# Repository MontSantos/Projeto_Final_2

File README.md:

# Do Material ao Digital

## Implementação de Jogos e Utilitários em Hardware Reprogramável

**Por: Guilherme Santos**  
Repositório de Projeto Final de Graduação em Engenharia de Computação.

Nota Final: 10,0 / 10,0

---

Este repositório disponibiliza todos os materiais utilizados e desenvolvidos ao longo do projeto, incluindo:

- Esquemáticos e layouts das PCBs desenvolvidas para suporte de periféricos
- Data sheets dos principais componentes utilizados
- Implementações de protocolos de comunicação de vídeo (VGA) e teclado (PS/2)
- Códigos de teste para validação de módulos
- Códigos completos dos projetos implementados no FPGA
- Simulações dos circuitos desenvolvidos

---

## Estrutura do Repositório

Este repositório está organizado da seguinte forma:

- **Datasheets**  
  Data sheets dos componentes utilizados nos projetos.

- **HDL_Projetos**  
  Códigos HDL completos dos projetos desenvolvidos, incluindo:
  - Pong
  - Breakout
  - Interface de desenho (Paint)
  - Sintetizador de áudio utilizando teclado PS/2

- **HDL_Testes**  
  Códigos de teste para validação e depuração dos módulos.

- **LTspice_Sims**  
  Simulações realizadas no LTspice para análise de circuitos.

- **PCB_Projetos**  
  Esquemáticos e layouts das PCBs desenvolvidas.

- **Resistor**  
  Script para cálculo e organização de resistores para o VGA.

---

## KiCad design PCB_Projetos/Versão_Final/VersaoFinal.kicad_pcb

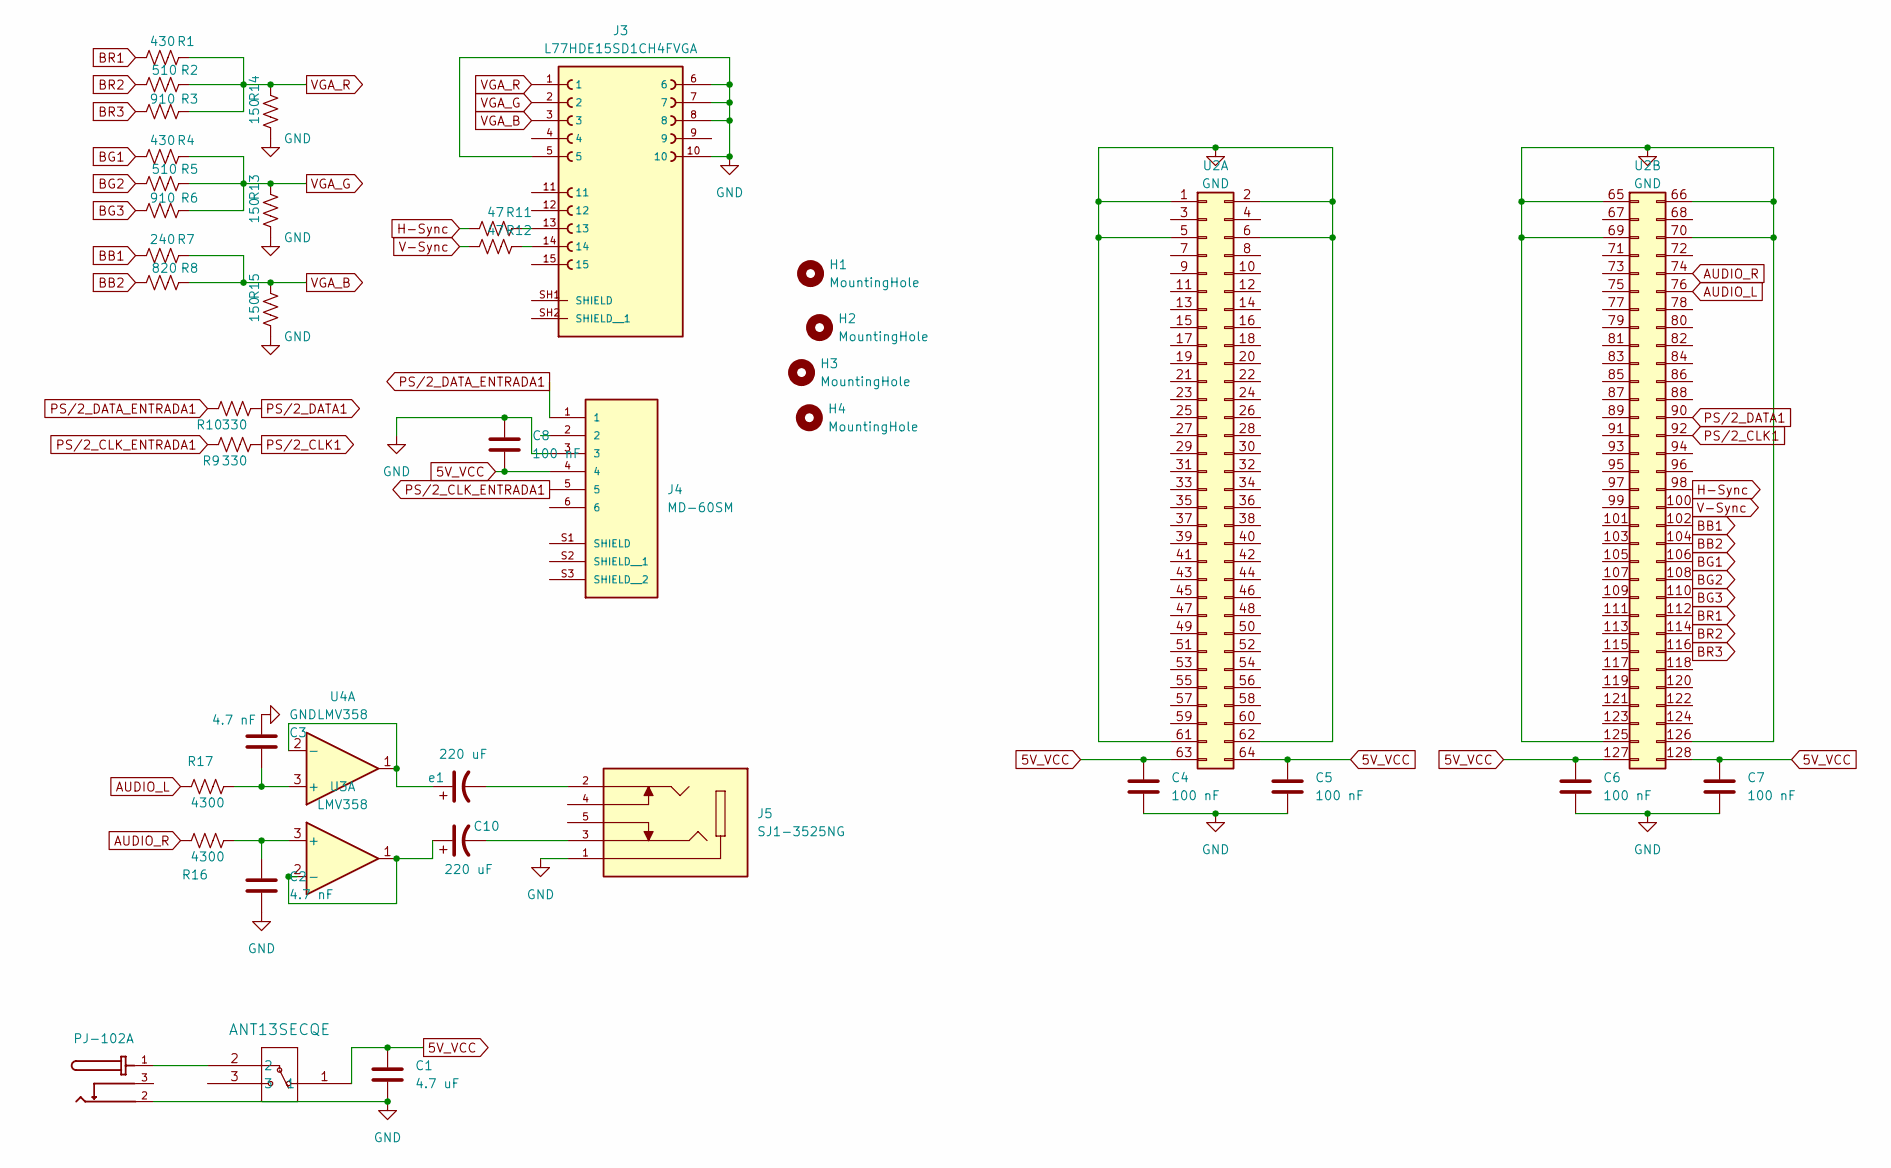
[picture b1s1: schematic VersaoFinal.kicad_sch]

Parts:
C1: 4.7 uF; C_Axial_L3.8mm_D2.6mm_P7.50mm_Horizontal
C2, C3: 4.7 nF; C_Axial_L3.8mm_D2.6mm_P7.50mm_Horizontal
C4, C5, C6, C7, C8: 100 nF; C_Axial_L3.8mm_D2.6mm_P7.50mm_Horizontal
C10: 220 uF; CP_Radial_D5.0mm_P2.00mm
H1, H2, H3, H4: MountingHole; MountingHole_2.2mm_M2
J2: PJ-102A; CUI_PJ-102A
J3: L77HDE15SD1CH4FVGA; AMPHENOL_L77HDE15SD1CH4FVGA; PARTREV 1
J4: MD-60SM; CUI_MD-60SM; PARTREV 02/18/2022
J5: SJ1-3525NG; CUI_SJ1-3525NG; PARTREV 1.01
R1, R4: 430; R_Axial_DIN0207_L6.3mm_D2.5mm_P7.62mm_Horizontal
R2, R5: 510; R_Axial_DIN0207_L6.3mm_D2.5mm_P7.62mm_Horizontal
R3, R6: 910; R_Axial_DIN0207_L6.3mm_D2.5mm_P7.62mm_Horizontal
R7: 240; R_Axial_DIN0207_L6.3mm_D2.5mm_P7.62mm_Horizontal
R8: 820; R_Axial_DIN0207_L6.3mm_D2.5mm_P7.62mm_Horizontal
R9, R10: 330; R_Axial_DIN0207_L6.3mm_D2.5mm_P7.62mm_Horizontal
R11, R12: 47; R_Axial_DIN0207_L6.3mm_D2.5mm_P7.62mm_Horizontal
R13, R14, R15: 150; R_Axial_DIN0207_L6.3mm_D2.5mm_P7.62mm_Horizontal
R16, R17: 4300; R_Axial_DIN0207_L6.3mm_D2.5mm_P7.62mm_Horizontal
U1: ANT13SECQE; ANT13SEC_CRS
U2: Placa
U3, U4: LMV358
e1: 220 uF; CP_Radial_D5.0mm_P2.00mm

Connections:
5V_VCC: C1.1, C4.1, C5.1, C6.1, C7.1, C8.2, J4.4, U1.1, U2.63, U2.64, U2.127, U2.128
AUDIO_L: R17.1, U2.76
AUDIO_R: R16.1, U2.74
BB1: R7.2, U2.102
BB2: R8.2, U2.104
BG1: R4.2, U2.106
BG2: R5.2, U2.108
BG3: R6.2, U2.110
BR1: R1.2, U2.112
BR2: R2.2, U2.114
BR3: R3.2, U2.116
GND: C1.2, C2.2, C3.1, C4.2, C5.2, C6.2, C7.2, C8.1, J2.2, J3.5, J3.6, J3.7, J3.8, J3.10, J4.3, J5.1, R13.2, R14.2, R15.2, U2.1, U2.2, U2.5, U2.6, U2.61, U2.62, U2.65, U2.66, U2.69, U2.70, U2.125, U2.126
H-Sync: R11.2, U2.98
unnamed: C10.2, J5.3
unnamed: J2.1, U1.2
unnamed: J3.13, R11.1
unnamed: J3.14, R12.1
unnamed: J5.2, e1.2
unnamed: C2.1, R16.2, U3.3 (+)
unnamed: C10.1, U3.1, U3.2 (-)
unnamed: C3.2, R17.2, U4.3 (+)
unnamed: U4.1, U4.2 (-), e1.1
PS/2_CLK1: R9.2, U2.92
PS/2_CLK_ENTRADA1: J4.5, R9.1
PS/2_DATA1: R10.2, U2.90
PS/2_DATA_ENTRADA1: J4.1, R10.1
V-Sync: R12.2, U2.100
VGA_B: J3.3, R7.1, R8.1, R15.1
VGA_G: J3.2, R4.1, R5.1, R6.1, R13.1
VGA_R: J3.1, R1.1, R2.1, R3.1, R14.1

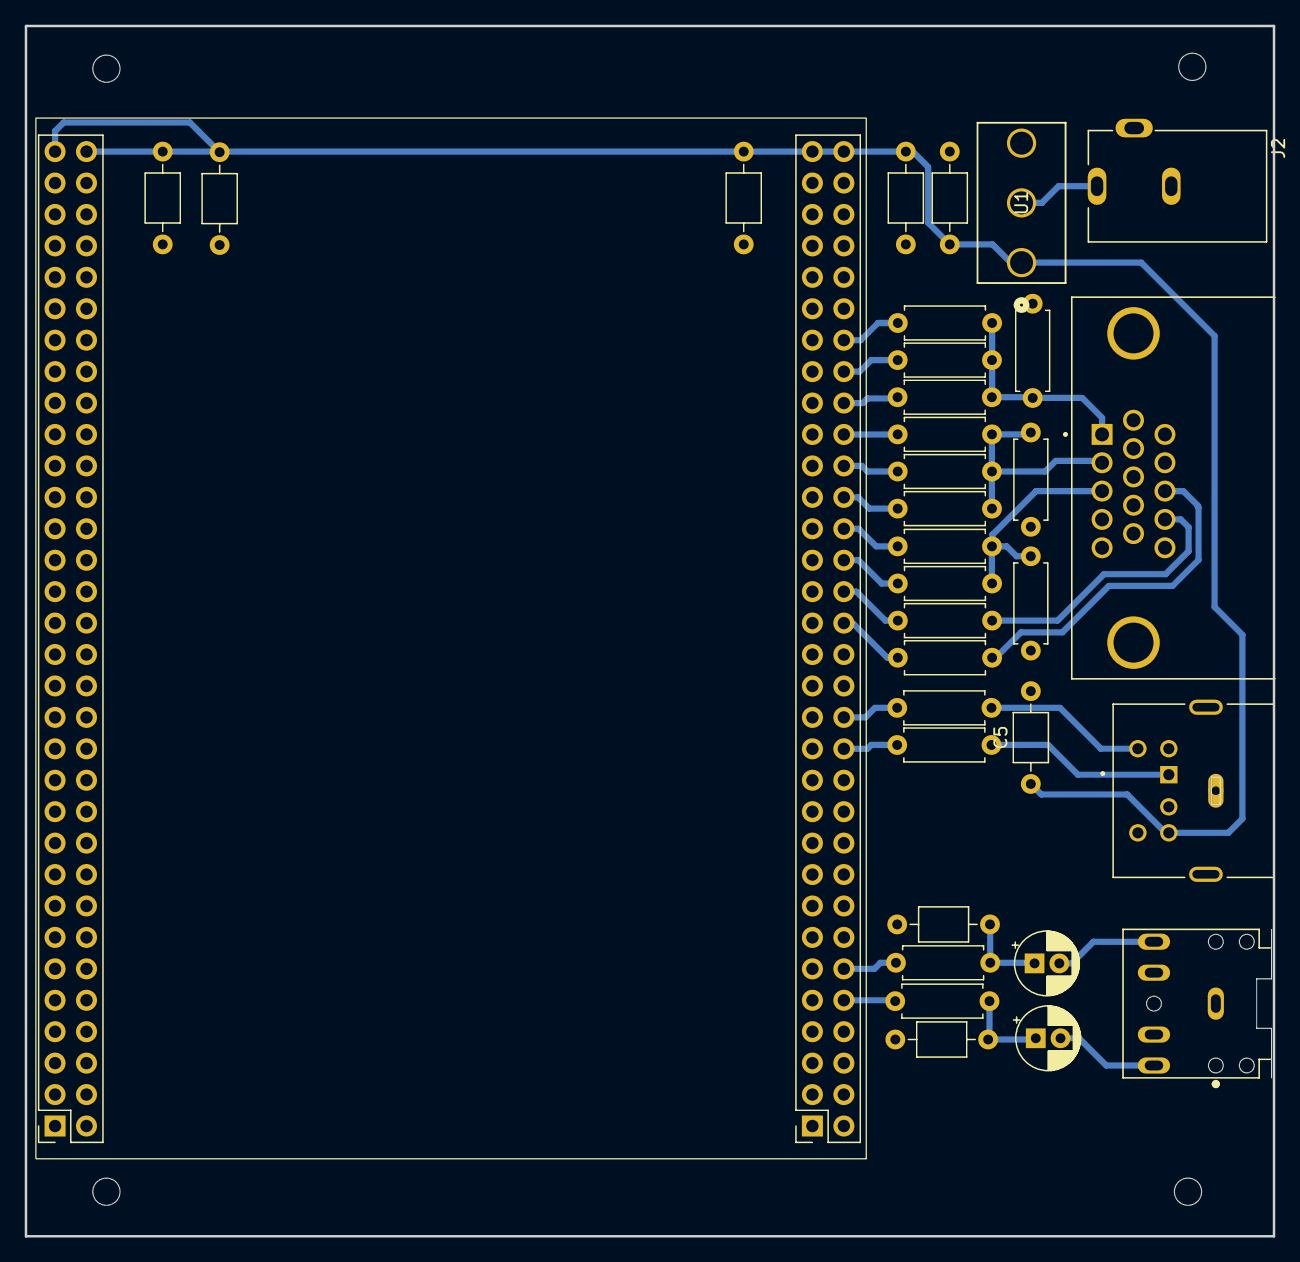
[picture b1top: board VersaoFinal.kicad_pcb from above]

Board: 2 copper layers, 100.8 x 97.8 mm, 37 parts (0 on the bottom side), 28 nets.

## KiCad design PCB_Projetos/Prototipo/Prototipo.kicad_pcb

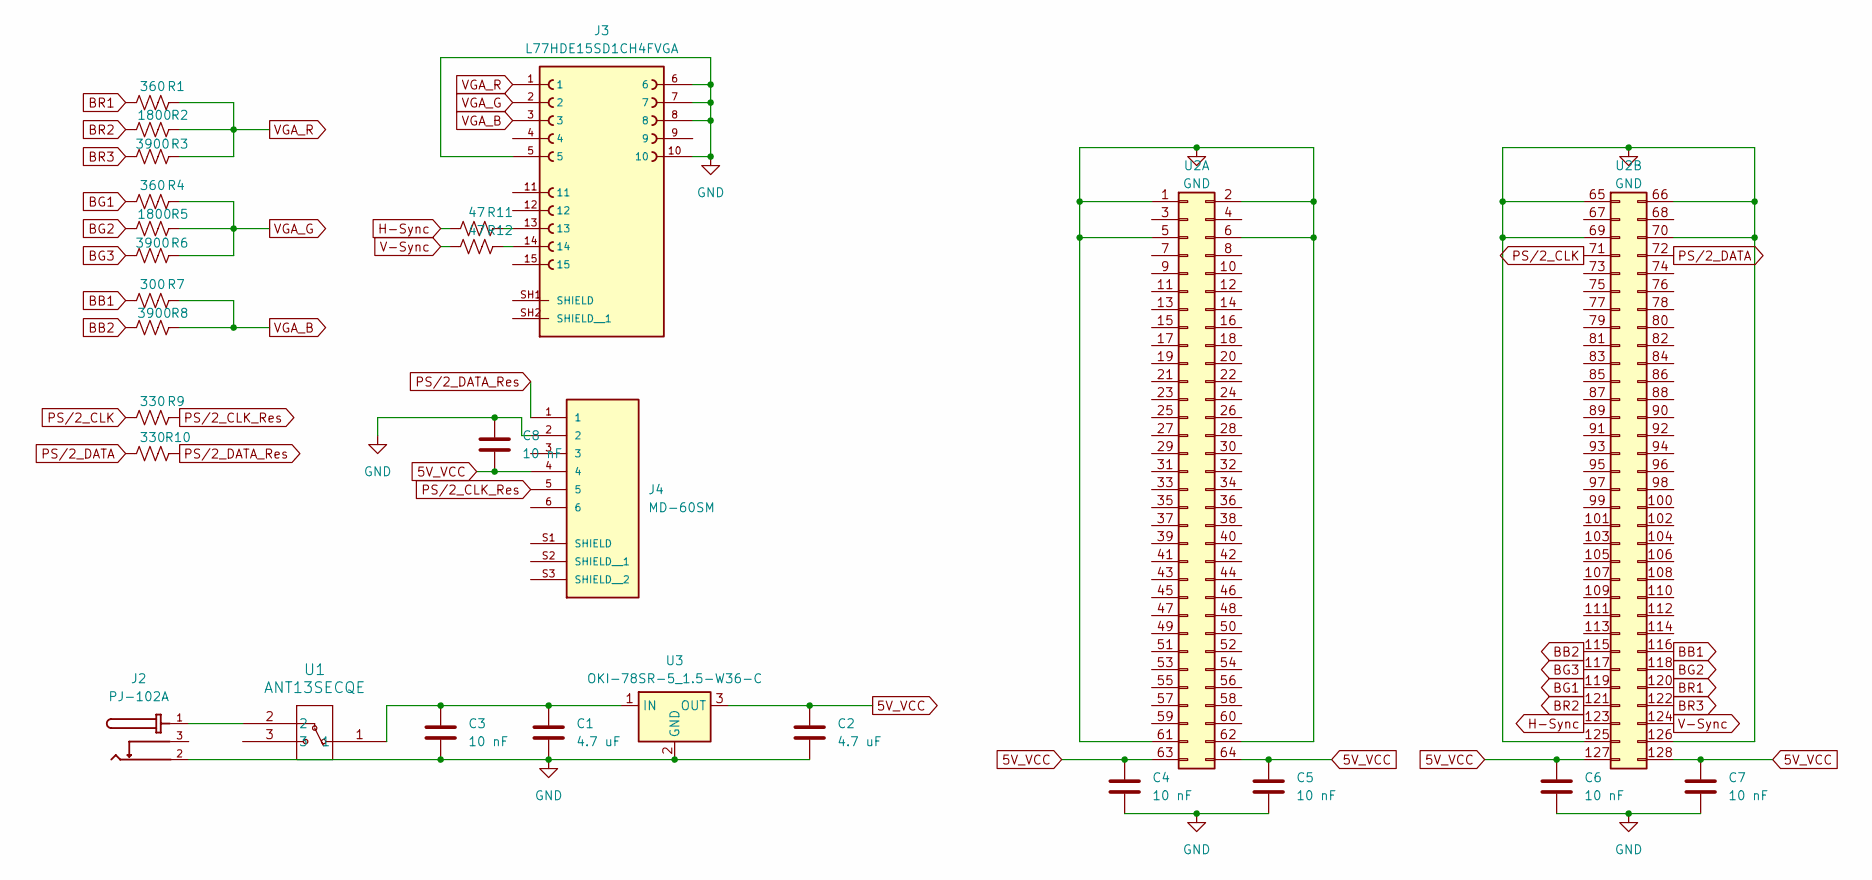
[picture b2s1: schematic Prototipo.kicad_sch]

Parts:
C1, C2: 4.7 uF; C_Axial_L3.8mm_D2.6mm_P7.50mm_Horizontal
C3, C4, C5, C6, C7, C8: 10 nF; C_Axial_L3.8mm_D2.6mm_P7.50mm_Horizontal
J2: PJ-102A; CUI_PJ-102A
J3: L77HDE15SD1CH4FVGA; AMPHENOL_L77HDE15SD1CH4FVGA; PARTREV 1
J4: MD-60SM; CUI_MD-60SM; PARTREV 02/18/2022
R1, R4: 360; R_Axial_DIN0207_L6.3mm_D2.5mm_P7.62mm_Horizontal
R2, R5: 1800; R_Axial_DIN0207_L6.3mm_D2.5mm_P7.62mm_Horizontal
R3, R6, R8: 3900; R_Axial_DIN0207_L6.3mm_D2.5mm_P7.62mm_Horizontal
R7: 300; R_Axial_DIN0207_L6.3mm_D2.5mm_P7.62mm_Horizontal
R9, R10: 330; R_Axial_DIN0207_L6.3mm_D2.5mm_P7.62mm_Horizontal
R11, R12: 47; R_Axial_DIN0207_L6.3mm_D2.5mm_P7.62mm_Horizontal
U1: ANT13SECQE; ANT13SEC_CRS
U2: Placa
U3: OKI-78SR-5_1.5-W36-C; Converter_DCDC_Murata_OKI-78SR_Vertical

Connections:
5V_VCC: C2.1, C4.1, C5.1, C6.1, C7.1, C8.2, J4.4, U2.63, U2.64, U2.127, U2.128, U3.3 (OUT)
BB1: R7.2, U2.116
BB2: R8.2, U2.115
BG1: R4.2, U2.119
BG2: R5.2, U2.118
BG3: R6.2, U2.117
BR1: R1.2, U2.120
BR2: R2.2, U2.121
BR3: R3.2, U2.122
GND: C1.2, C2.2, C3.2, C4.2, C5.2, C6.2, C7.2, C8.1, J2.2, J3.5, J3.6, J3.7, J3.8, J3.10, J4.2, U2.1, U2.2, U2.5, U2.6, U2.61, U2.62, U2.65, U2.66, U2.69, U2.70, U2.125, U2.126, U3.2 (GND)
H-Sync: R11.2, U2.123
unnamed: J2.1, U1.2
unnamed: J3.13, R11.1
unnamed: J3.14, R12.1
unnamed: C1.1, C3.1, U1.1, U3.1 (IN)
PS/2_CLK: R9.2, U2.71
PS/2_CLK_Res: J4.5, R9.1
PS/2_DATA: R10.2, U2.72
PS/2_DATA_Res: J4.1, R10.1
V-Sync: R12.2, U2.124
VGA_B: J3.3, R7.1, R8.1
VGA_G: J3.2, R4.1, R5.1, R6.1
VGA_R: J3.1, R1.1, R2.1, R3.1

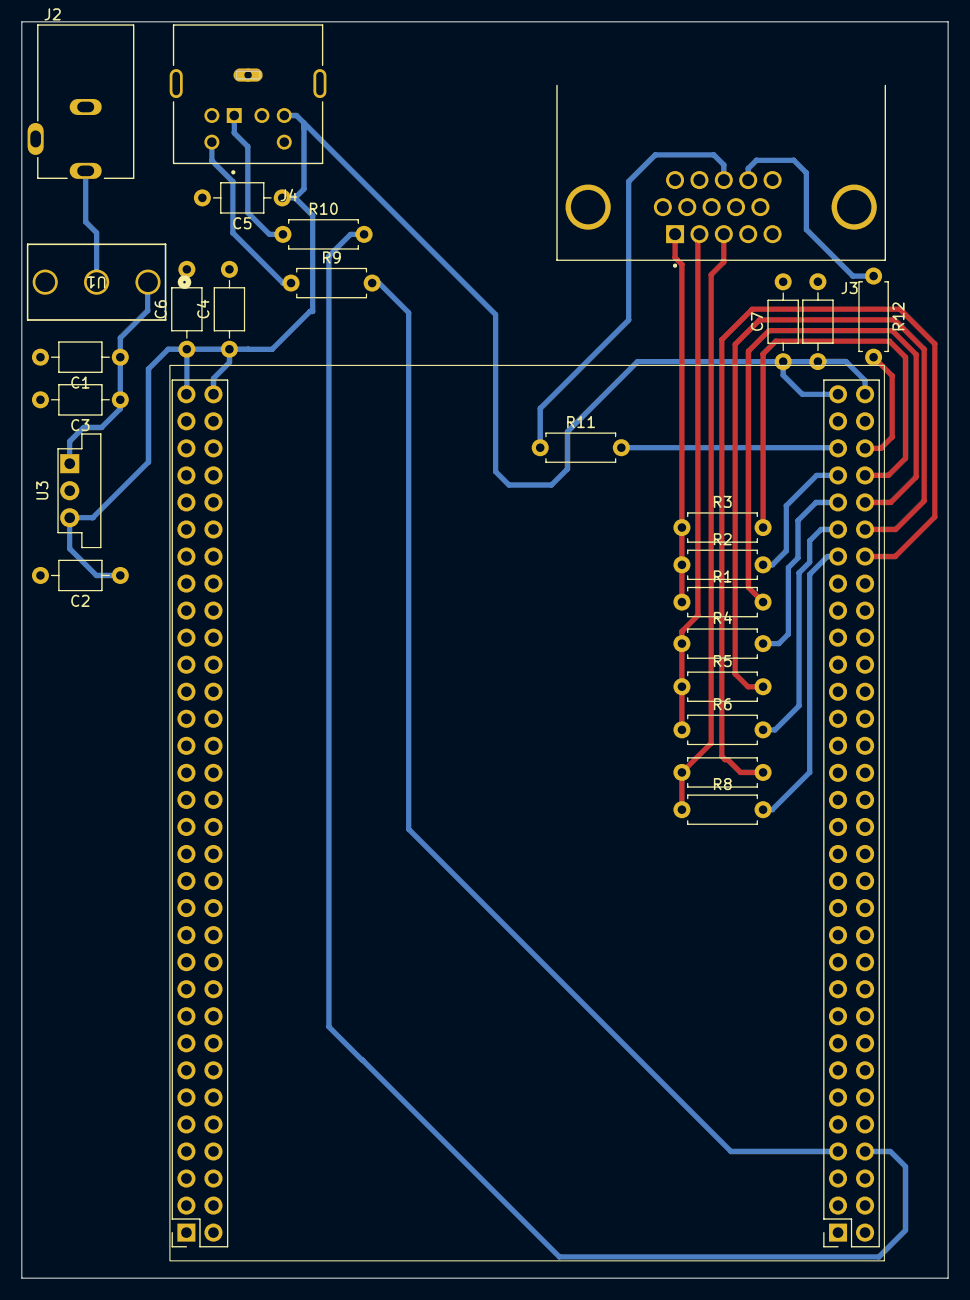
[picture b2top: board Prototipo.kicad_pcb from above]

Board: 2 copper layers, 87.0 x 118.0 mm, 26 parts (0 on the bottom side), 23 nets.

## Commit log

2025-07-05 License e calc de resistor
2025-07-05 Adicionando os testes
2025-07-05 Adicionando Projetos
2025-07-05 Adicionando mais projetos
2025-07-05 Adicionando Simulações
2025-07-05 Adicionando simulaçoes e biblioteca de comps
2025-07-05 retirando
2025-07-05 Adicionando DataSheets
2025-07-05 Adicionando PCB`s
2025-07-05 Rename License.txt to LICENSE
2025-07-05 Update LICENSE
2025-07-06 Correçao
2025-07-06 Mais correçoes
2025-07-06 Alteração
